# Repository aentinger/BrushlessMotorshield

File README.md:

💾 Brushless Motorshield
========================

# 📸 Image

# 📂 Description

The Brushless Motorshield facilitates the control of a brushless motor with high performance (up to 46 A per phase). Furthermore so-called brushless gimbal motors can be controlled. For a quick and easy start, an open source Arduino library with sample programs is available.

**Features**

* Control of a brushless motor (BLDC Motor)
* Control of a Brushless Gimbal Motor
* Voltage supply range: 7.4 -14.8 V
* Can be used with 2S, 3S and 4S LiPo-battery
* High performance: Maximum continuous output current per phase: 46 A
* Motor drivers are protected against short circuit (to ground/supply), overheating, overvoltage and undervoltage
* Arduino Library with example programs is available on GitHub

# 🎥 [Video](images/brushless_motorshield_demo.mp4)

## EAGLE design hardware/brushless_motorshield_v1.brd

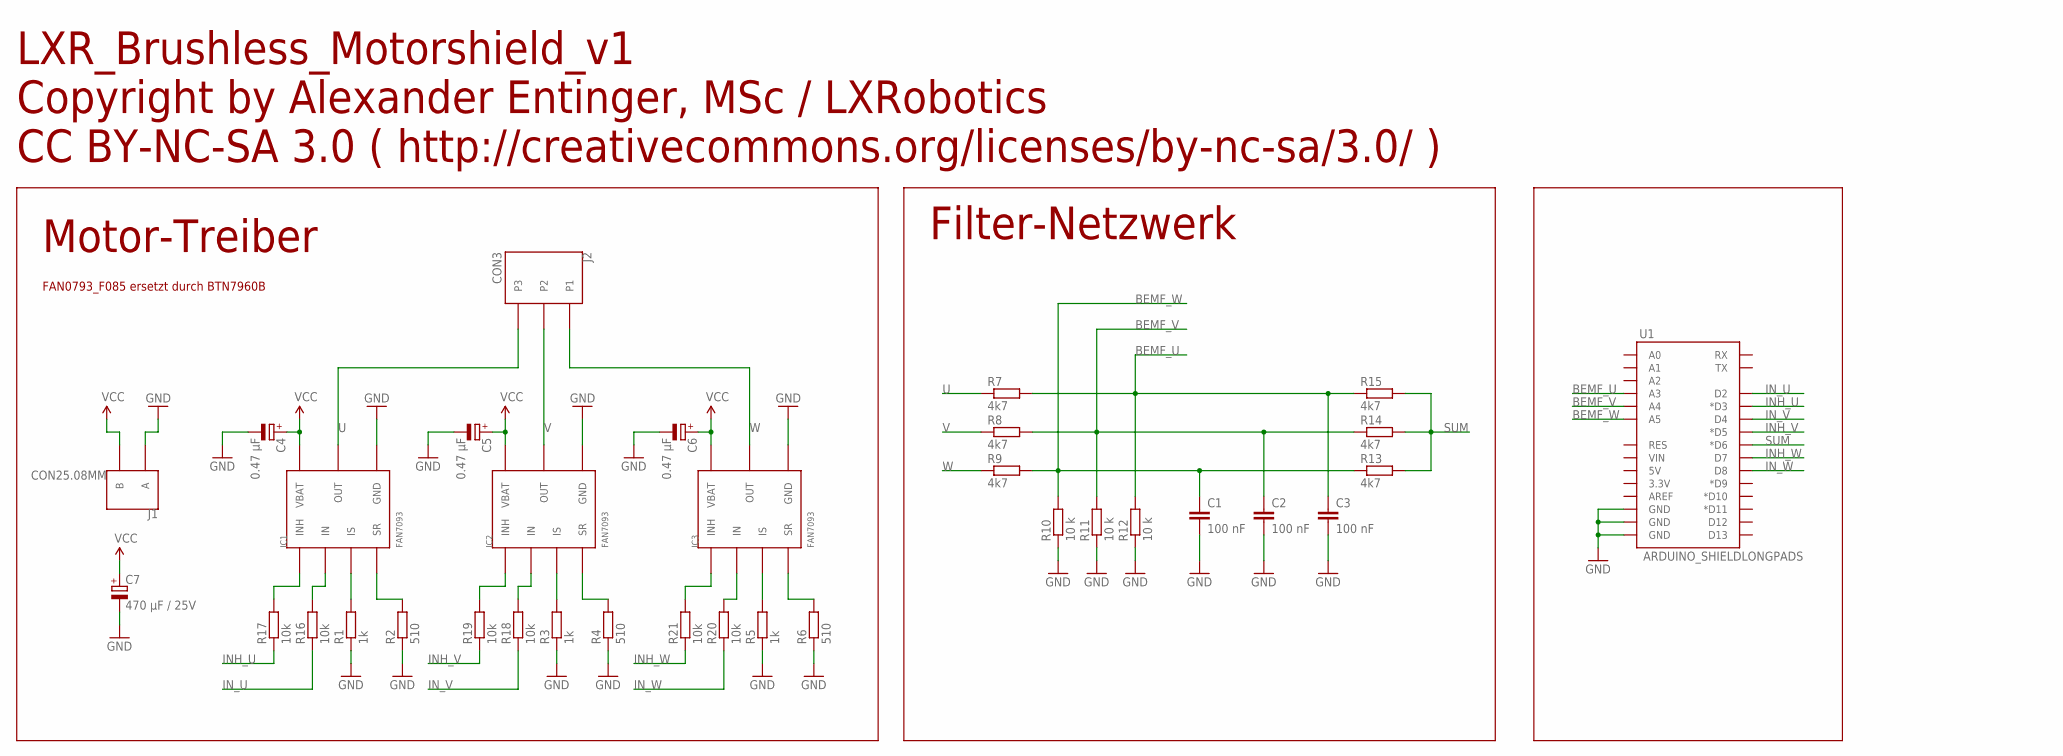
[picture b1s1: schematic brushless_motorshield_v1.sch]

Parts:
C1, C2, C3: 100 nF; C0805
C4, C5, C6: 0.47 µF; KEMET_A
C7: 470 µF / 25V; E5-10,5
IC1, IC2, IC3: FAN7093; TO263-7L
J1: CON25.08MM; CON2_SCHRAUBKLEMME
J2: CON3; CON3_SCHRAUBKLEMME
R1, R3, R5: 1k; R0805
R2, R4, R6: 510; R0805
R7, R8, R9, R13, R14, R15: 4k7; R0805
R10, R11, R12: 10 k; R0805
R16, R17, R18, R19, R20, R21: 10k; R0805
U1: ARDUINO_SHIELDLONGPADS; DUEMILANOVE_SHIELD_LONGPADS

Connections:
BEMF_U: C3.1, R7.2, R12.2, R15.1, U1.A3
BEMF_V: C2.1, R8.2, R11.2, R14.1, U1.A4
BEMF_W: C1.1, R9.2, R10.2, R13.1, U1.A5
GND: C1.2, C2.2, C3.2, C4.CATHODE (-), C5.CATHODE (-), C6.CATHODE (-), C7.-, IC1.GND, IC2.GND, IC3.GND, J1.1 (A), R1.1, R2.1, R3.1, R4.1, R5.1, R6.1, R10.1, R11.1, R12.1, U1.GND@0 (GND), U1.GND@1 (GND), U1.GND@2 (GND)
INH_U: R17.1, U1.D3 (*D3)
INH_V: R19.1, U1.D5 (*D5)
INH_W: R21.1, U1.D7
IN_U: R16.1, U1.D2
IN_V: R18.1, U1.D4
IN_W: R20.1, U1.D8
unnamed: IC1.IS, R1.2
unnamed: IC1.SR, R2.2
unnamed: IC2.IS, R3.2
unnamed: IC2.SR, R4.2
unnamed: IC3.IS, R5.2
unnamed: IC3.SR, R6.2
unnamed: IC1.INH, R17.2
unnamed: IC1.IN, R16.2
unnamed: IC3.INH, R21.2
unnamed: IC3.IN, R20.2
unnamed: IC2.INH, R19.2
unnamed: IC2.IN, R18.2
SUM: R13.2, R14.2, R15.2, U1.D6 (*D6)
U: IC1.OUT, IC1.OUT@1 (OUT), J2.P3, R7.1
V: IC2.OUT, IC2.OUT@1 (OUT), J2.P2, R8.1
VCC: C4.ANODE (+), C5.ANODE (+), C6.ANODE (+), C7.+, IC1.VBATT (VBAT), IC2.VBATT (VBAT), IC3.VBATT (VBAT), J1.2 (B)
W: IC3.OUT, IC3.OUT@1 (OUT), J2.P1, R9.1

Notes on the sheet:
LXR_Brushless_Motorshield_v1 Copyright by Alexander Entinger, MSc / LXRobotics CC BY-NC-SA 3.0 ( http://creativecommons.org/licenses/by-nc-sa/3.0/ )
Motor-Treiber
Filter-Netzwerk
FAN0793_F085 ersetzt durch BTN7960B

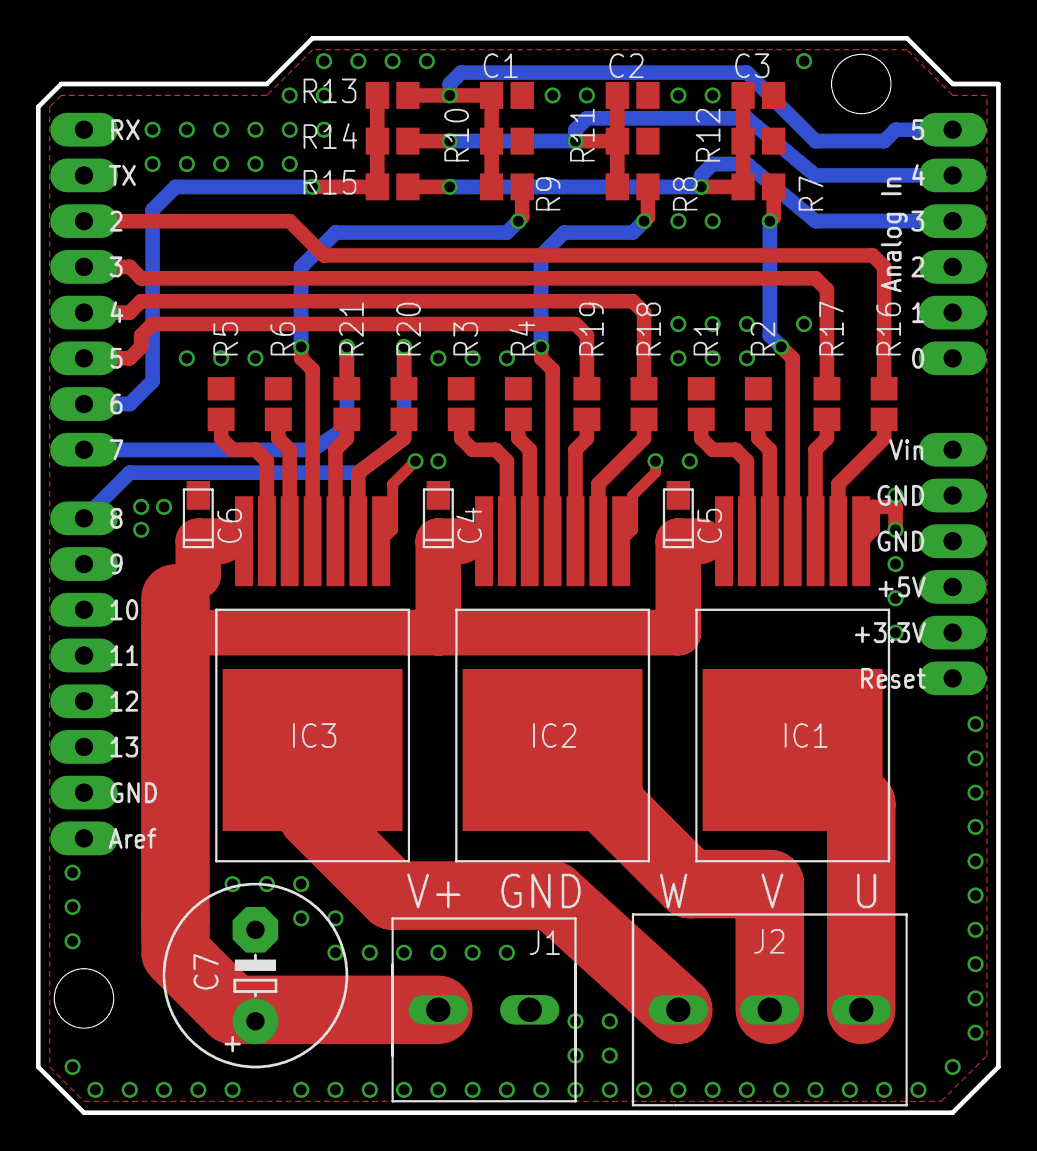
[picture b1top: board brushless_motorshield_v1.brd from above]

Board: 2 copper layers, 53.3 x 59.7 mm, 34 parts (0 on the bottom side), 27 nets.

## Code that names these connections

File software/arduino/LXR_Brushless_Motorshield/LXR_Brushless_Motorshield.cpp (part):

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#define AC_INT_PORT		(PORTB)
#define AC_INT			(1<<1)
#endif
// IN_W = D8 = PB0
#define IN_W_DDR		(DDRB)
#define IN_W_PORT		(PORTB)
#define IN_W			(1<<0)
// INH_W = D7 = PD7
#define INH_W_DDR		(DDRD)
#define INH_W_PORT		(PORTD)
#define INH_W			(1<<7)
// IN_V = D4 = PD4
#define IN_V_DDR		(DDRD)
#define IN_V_PORT		(PORTD)
#define IN_V			(1<<4)
// INH_V = D5 = PD5
#define INH_V_DDR		(DDRD)
#define INH_V_PORT		(PORTD)
#define INH_V			(1<<5)
// IN_U = D2 = PD2
#define IN_U_DDR		(DDRD)
#define IN_U_PORT		(PORTD)
#define IN_U			(1<<2)
// INH_U = D3 = PD3
#define INH_U_DDR		(DDRD)
#define INH_U_PORT		(PORTD)
#define INH_U			(1<<3)
// MUX settings for connecting the bemf pin to the AIN1 input of the analog comparator
// BEMF_W = A5 = ADC5
#define MUX_BEMF_W_TO_AIN1	ADMUX &= 0xF0; ADMUX |= (1<<MUX2) | (1<<MUX0);
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  // init the analog comparator
  // turn off adc
  ADCSRA &= ~(1<<ADEN);
  // turn off the digital input buffer on the pin AIN0 (PD6, SUM Signal)
  DIDR1 |= (1<<AIN0D);
  // turn off the digital input buffer on the pins ADC5, ADC4, ADC3
  DIDR0 |= (1<<ADC5D) | (1<<ADC4D) | (1<<ADC3D);
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
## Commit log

2013-11-28 changed readme
2014-01-15 initial checkin for brushless motorshield
2014-04-25 adding direction control for brushless motorshield
2014-04-30 adding library for control of brushless gimbal motors
2014-08-20 FAN7093_F085 replaced with BTN7960B
2015-10-08 bugfix by marco schilling (tu illmenau) - comparator interrupt is only enabled if speed is greater than zero - otherwise electrical noise can lead to an undesired positive feedback effect
2015-11-26 fixed small bug causing software not to work properly because TCCR2A is preset by arduino environment (init-function)
2015-11-26 adding source code for gimbal space vector modulation control
2017-06-26 Adding hardware files and images
2025-03-26 Add BOM.
2025-03-26 Upload demo video.
2025-03-26 Pretty up README.

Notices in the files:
software/arduino/LXR_Brushless_Motorshield/LXR_Brushless_Motorshield.cpp:
@license Attribution-NonCommercial-ShareAlike 3.0 Unported (CC BY-NC-SA 3.0) ( http://creativecommons.org/licenses/by-nc-sa/3.0/ )
README.md:
License: CC BY-NC-SA 4.0
parts and their libraries:
SparkFun-Boards: Licensing: CC v3.0 Share-Alike You are welcome to use this library for commercial purposes.
